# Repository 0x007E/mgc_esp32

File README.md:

# `MGC_module` - ESP32

The `ESP32` (`mgc_module`) is an adaptable board for the [MeGARCard](https://github.com/0x007e/mgc). The board offers the possibility to control the `MeGARCard` with an [ESP32](#additional-information). The board itself is connected to the `MeGARCard` within the pcb-to-pcb connectors (no soldering necessary). With the onboard dip-switches the boot setup and the port expander `twi` address can be modified. The board itself operates with `3V3` deliverd from the `MeGARCard`.

> To mount the board on the `MeGARCard` disconnect the power source (`USB-C` connector) or any other used source from the MeGARCard!

| Experience  | Level                                                                               |
|:------------|:-----------------------------------------------------------------------------------:|
| Soldering   |  |

# Downloads

| Type      | File                                                                                                                                                 | Description     |
|:---------:|:----------------------------------------------------------------------------------------------------------------------------------------------------:|:----------------|
| Schematic | [pdf](https://github.com/0x007E/mgc_esp32/releases/latest/download/schematic.pdf) / [cadlab](https://cadlab.io/project/30425/main/files)                   | Schematic files |
| Board     | [pdf](https://github.com/0x007E/mgc_esp32/releases/latest/download/pcb.pdf) / [cadlab](https://cadlab.io/project/30425/main/files)                         | Board file      |
| Drill     | [pdf](https://github.com/0x007E/mgc_esp32/releases/latest/download/drill.pdf)                                                                              | Drill file      |
| BoM | [xlsx](https://github.com/0x007E/mgc_esp32/releases/latest/download/bom.xlsx) / [html](https://github.com/0x007E/mgc_esp32/releases/latest/download/ibom.html)          | Bill of Material as Excel/interactive HTML |
| PCB    | [zip](https://github.com/0x007E/mgc_esp32/releases/latest/download/kicad.zip) / [tar](https://github.com/0x007E/mgc_esp32/releases/latest/download/kicad.tar.gz)    | KiCAD/Gerber/BoM/Drill files       |

# Hardware

The pcb is created with `KiCAD`. All files are built with `github actions` so that they are ready for a production environment.

## PCB

The circuit board is populated on both sides (Top, Bottom). The best way for soldering the `SMD` components is within a vapor phase soldering system and for the `THT` components with a standard soldering system.

### Top Layer

### Bottom Layer

# Additional Information

| Type       | Link               | Description              |
|:----------:|:------------------:|:-------------------------|
| ESP32  | [pdf](https://documentation.espressif.com/esp32-wroom-32e_esp32-wroom-32ue_datasheet_en.pdf) | ESP32-WROOM-32UE Datasheet |

---

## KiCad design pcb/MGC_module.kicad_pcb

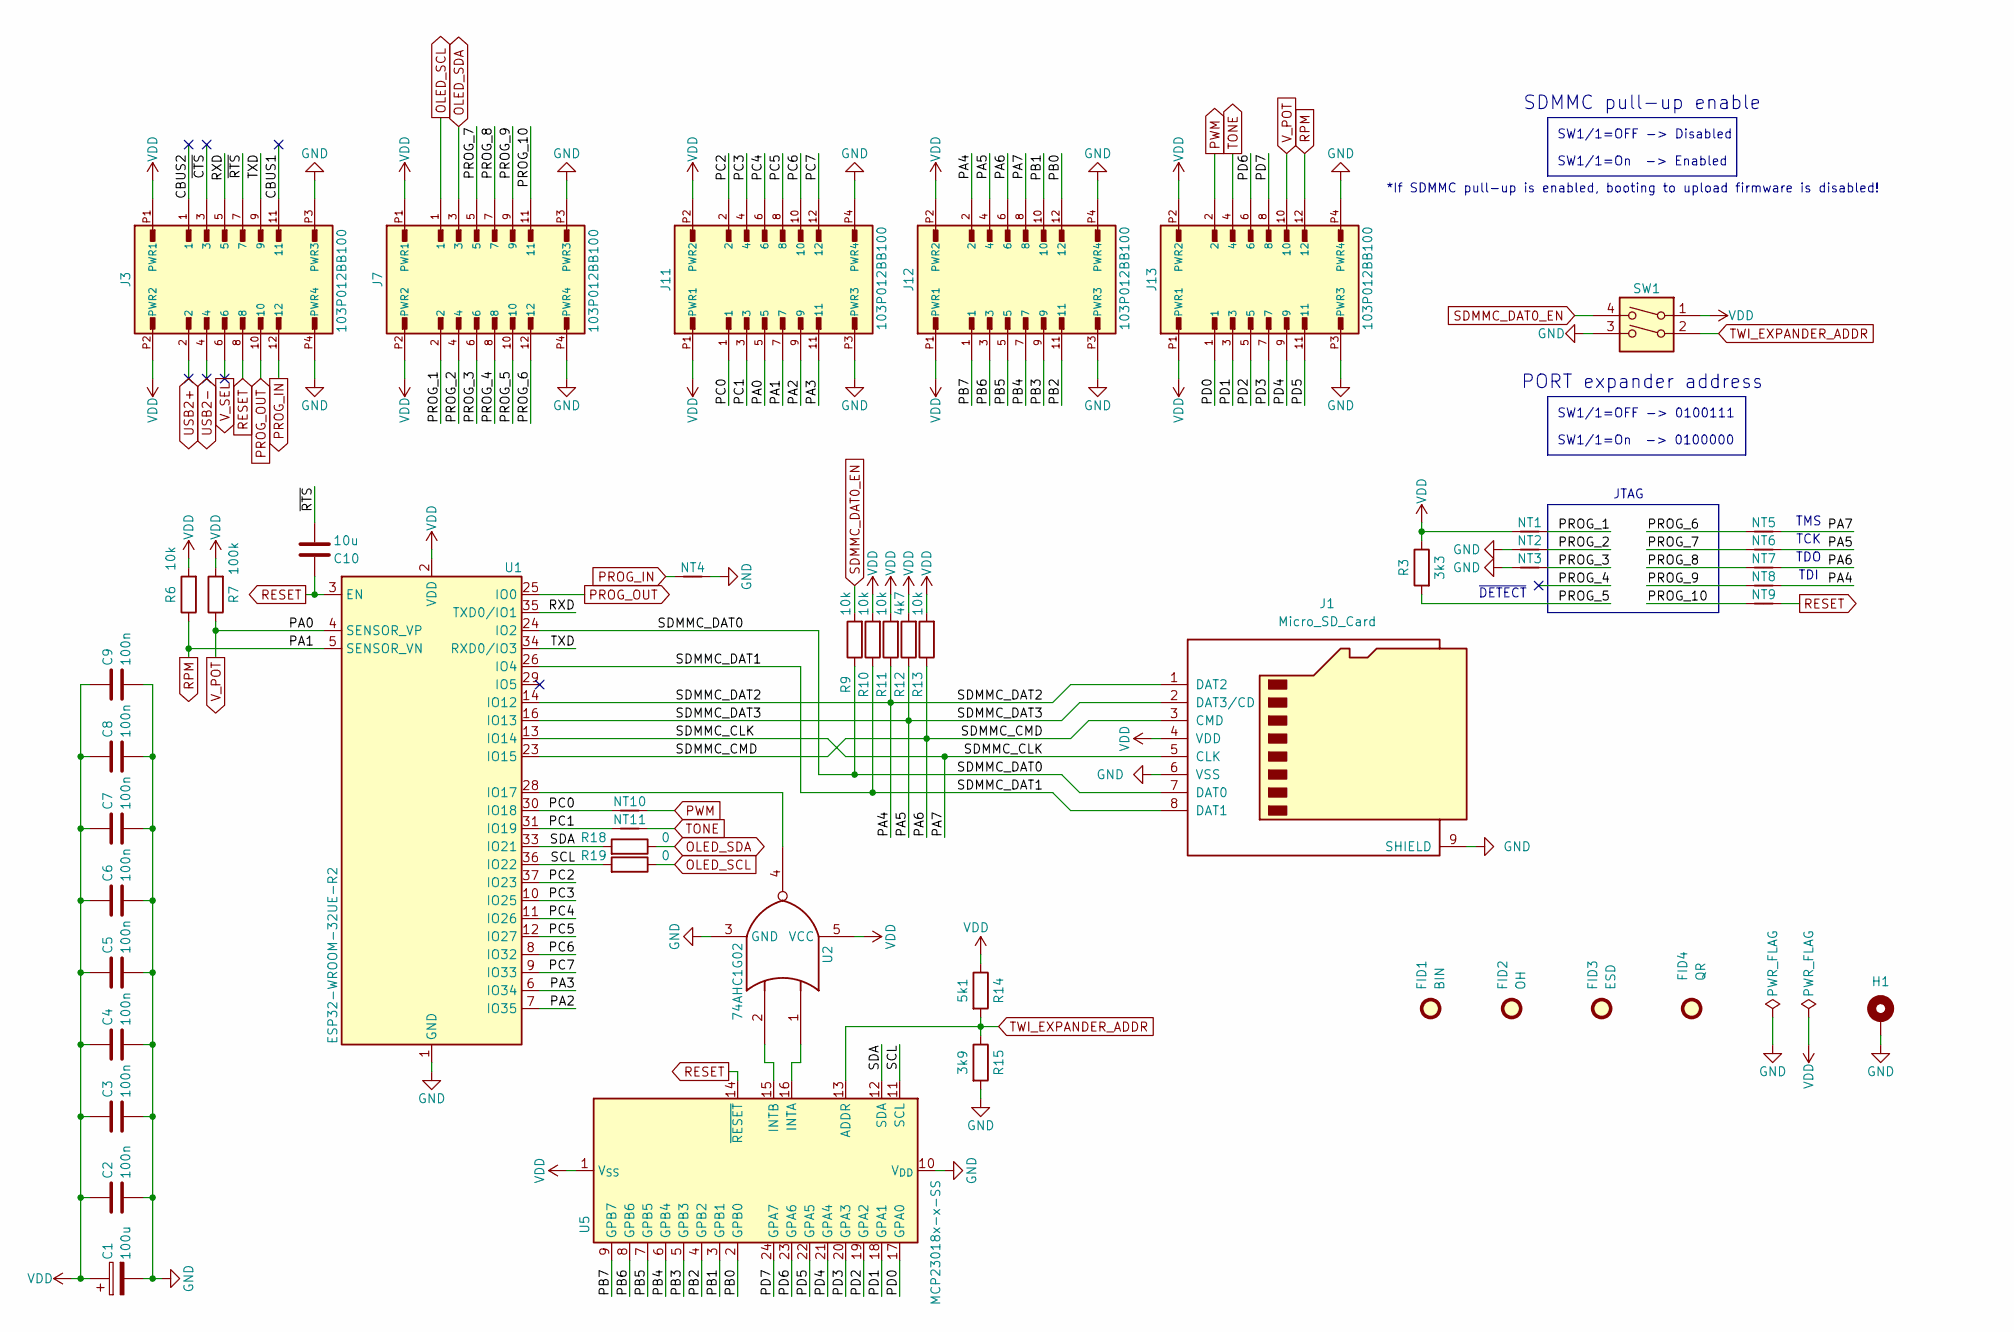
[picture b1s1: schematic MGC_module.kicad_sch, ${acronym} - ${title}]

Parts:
C1: 100u; CP_EIA-3528-21_Kemet-B; DigiKey 478-3877-1-ND
C2, C3, C4, C5, C6, C7, C8, C9: 100n; C_1206_3216Metric
C10: 10u; C_1206_3216Metric
FID1: BIN; WEEE-Logo_4.2x6mm_SilkScreen
FID2: OH; OSHW-Logo2_7.3x6mm_SilkScreen
FID3: ESD; ESD-Logo_6.6x6mm_SilkScreen
FID4: QR; QR_0x007e_very_small
H1: MountingHole_Pad; MountingHole_2.7mm_M2.5_DIN965_Pad
J1: Micro_SD_Card; microSD_HC_Molex_47219-2001; DigiKey WM6698CT-ND
J3, J7, J11, J12, J13: 103P012BB100; AMPHENOL_103P012BB100; DigiKey 609-103P012BB100CT-ND
NT1, NT2, NT3, NT4, NT5, NT6, NT7, NT8, NT9, NT10, NT11: NetTie_2; NetTie-2_SMD_Pad0.5mm
R3: 3k3; R_1206_3216Metric
R6, R9, R10, R11, R13: 10k; R_1206_3216Metric
R7: 100k; R_1206_3216Metric
R12: 4k7; R_1206_3216Metric
R14: 5k1; R_1206_3216Metric
R15: 3k9; R_1206_3216Metric
R18, R19: 0; R_1206_3216Metric
SW1: SW_DIP_x02; SW_DIP_SPSTx02_Slide_6.7x6.64mm_W6.73mm_P2.54mm_LowProfile_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
U1: ESP32-WROOM-32UE-R2; ESP32-WROOM-32U; DigiKey 1965-ESP32-WROOM-32UE-N4CT-ND, WM12219-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
U2: 74AHC1G02; SOT-23-5; DigiKey 296-8742-1-ND
U5: MCP23018x-x-SS; SSOP-24_5.3x8.2mm_P0.65mm; DigiKey 150-MCP23018T-E/SSCT-ND

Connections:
/CBUS1: J3.11
/CBUS2: J3.1
/PA2: J11.9, U1.7 (IO35)
/PA3: J11.11, U1.6 (IO34)
/PA4: J1.1 (DAT2), J12.2, NT8.2, R11.1, U1.14 (IO12)
/PA5: J1.2 (DAT3/CD), J12.4, NT6.2, R12.1, U1.16 (IO13)
/PA6: J1.3 (CMD), J12.6, NT7.2, R13.1, U1.23 (IO15)
/PA7: J1.5 (CLK), J12.8, NT5.2, U1.13 (IO14)
/PB0: J12.12, U5.2 (GPB0)
/PB1: J12.10, U5.3 (GPB1)
/PB2: J12.11, U5.4 (GPB2)
/PB3: J12.9, U5.5 (GPB3)
/PB4: J12.7, U5.6 (GPB4)
/PB5: J12.5, U5.7 (GPB5)
/PB6: J12.3, U5.8 (GPB6)
/PB7: J12.1, U5.9 (GPB7)
/PC0: J11.1, NT10.1, U1.30 (IO18)
/PC1: J11.3, NT11.1, U1.31 (IO19)
/PC2: J11.2, U1.37 (IO23)
/PC3: J11.4, U1.10 (IO25)
/PC4: J11.6, U1.11 (IO26)
/PC5: J11.8, U1.12 (IO27)
/PC6: J11.10, U1.8 (IO32)
/PC7: J11.12, U1.9 (IO33)
/PD0: J13.1, U5.17 (GPA0)
/PD1: J13.3, U5.18 (GPA1)
/PD2: J13.5, U5.19 (GPA2)
/PD3: J13.7, U5.20 (GPA3)
/PD4: J13.9, U5.21 (GPA4)
/PD5: J13.11, U5.22 (GPA5)
/PD6: J13.6, U5.23 (GPA6)
/PD7: J13.8, U5.24 (GPA7)
/PROG_1: J7.2, NT1.2
/PROG_2: J7.4, NT2.2
/PROG_3: J7.6, NT3.2
/PROG_4: J7.8
/PROG_5: J7.10, R3.2
/PROG_6: J7.12, NT5.1
/PROG_7: J7.5, NT6.1
/PROG_8: J7.7, NT7.1
/PROG_9: J7.9, NT8.1
/PROG_10: J7.11, NT9.1
/RXD: J3.5, U1.35 (TXD0/IO1)
/SCL: R19.2, U1.36 (IO22), U5.11 (SCL)
/SDA: R18.2, U1.33 (IO21), U5.12 (SDA)
/SDMMC_DAT0: J1.7 (DAT0), R9.1, U1.24 (IO2)
/SDMMC_DAT1: J1.8 (DAT1), R10.1, U1.26 (IO4)
/TXD: J3.9, U1.34 (RXD0/IO3)
/~CTS: J3.3
/~RTS: C10.2, J3.7
GND: C1.2, C2.2, C3.2, C4.2, C5.2, C6.2, C7.2, C8.2, C9.2, H1.1, J1.6 (VSS), J1.9 (SHIELD), J3.P3 (PWR3), J3.P4 (PWR4), J7.P3 (PWR3), J7.P4 (PWR4), J11.P3 (PWR3), J11.P4 (PWR4), J12.P3 (PWR3), J12.P4 (PWR4), J13.P3 (PWR3), J13.P4 (PWR4), NT2.1, NT3.1, NT4.2, R15.2, SW1.3, U1.1 (GND), U1.15 (GND), U1.38 (GND), U1.39 (GND), U2.3 (GND), U5.10 (V_{DD})
unnamed: U1.28 (IO17), U2.4
unnamed: U2.1, U5.16 (INTA)
unnamed: U2.2, U5.15 (INTB)
OLED_SCL: J7.1, R19.1
OLED_SDA: J7.3, R18.1
PROG_IN: J3.12, NT4.1
PROG_OUT: J3.10, U1.25 (IO0)
PWM: J13.2, NT10.2
RESET: C10.1, J3.8, NT9.2, U1.3 (EN), U5.14 (~RESET)
RPM: J11.7, J13.12, R6.1, U1.5 (SENSOR_VN)
SDMMC_DAT0_EN: R9.2, SW1.4
TONE: J13.4, NT11.2
TWI_EXPANDER_ADDR: R14.2, R15.1, SW1.2, U5.13 (ADDR)
USB2+: J3.2
USB2-: J3.4
VDD: C1.1, C2.1, C3.1, C4.1, C5.1, C6.1, C7.1, C8.1, C9.1, J1.4 (VDD), J3.P1 (PWR1), J3.P2 (PWR2), J7.P1 (PWR1), J7.P2 (PWR2), J11.P1 (PWR1), J11.P2 (PWR2), J12.P1 (PWR1), J12.P2 (PWR2), J13.P1 (PWR1), J13.P2 (PWR2), NT1.1, R3.1, R6.2, R7.2, R10.2, R11.2, R12.2, R13.2, R14.1, SW1.1, U1.2 (VDD), U2.5 (VCC), U5.1 (V_{SS})
V_POT: J11.5, J13.10, R7.1, U1.4 (SENSOR_VP)
V_SEL: J3.6

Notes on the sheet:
SW1/1=OFF -> Disabled
TMS
SW1/1=On -> Enabled
SW1/1=OFF -> 0100111
PORT expander address
*If SDMMC pull-up is enabled, booting to upload firmware is disabled!
SDMMC pull-up enable
~{DETECT}
SW1/1=On -> 0100000
JTAG
TCK
TDI
TDO

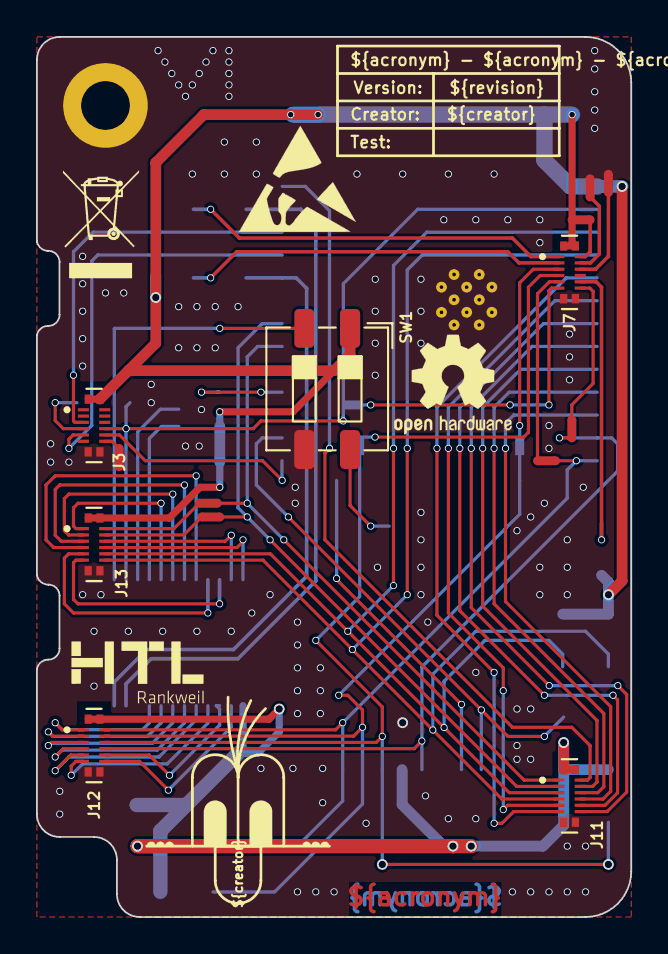
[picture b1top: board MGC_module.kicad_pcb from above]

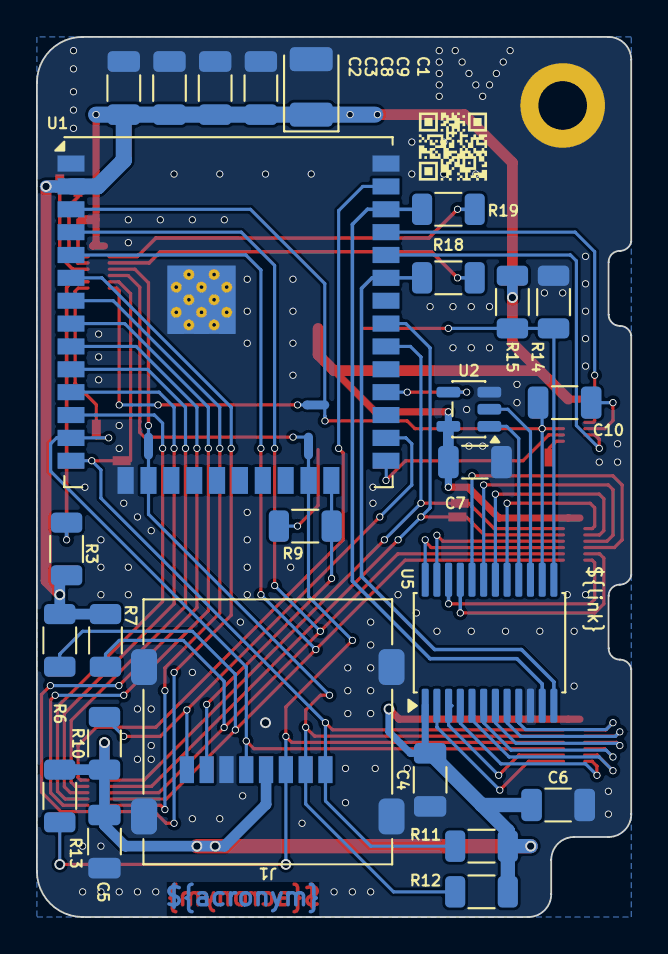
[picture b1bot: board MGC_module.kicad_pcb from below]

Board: 2 copper layers, 33.0 x 48.9 mm, 48 parts (30 on the bottom side), 62 nets.

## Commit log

2026-06-13 Add pcb layout
2026-06-13 Add missing vendor(id)
2026-06-18 Fix unconnected labels
2026-06-18 Add README.md
2026-06-18 Add build pipeline
2026-06-18 Add release pipeline
2026-06-23 Adapt output filenames
2026-06-23 Add missing values in bom
2026-06-23 Adapt config and update action versions
2026-06-23 Optimize ibom view

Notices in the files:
README.md:
License CC By-NC-SA
parts and their libraries:
license: CC BY-NC-SA 4.0
